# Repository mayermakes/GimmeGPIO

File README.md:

# GimmeGPIO
hardware to add GPIO to any PC running Linux

basic test, pins and pwm working
updated FW
python library working.
pushed changes.
case fits.

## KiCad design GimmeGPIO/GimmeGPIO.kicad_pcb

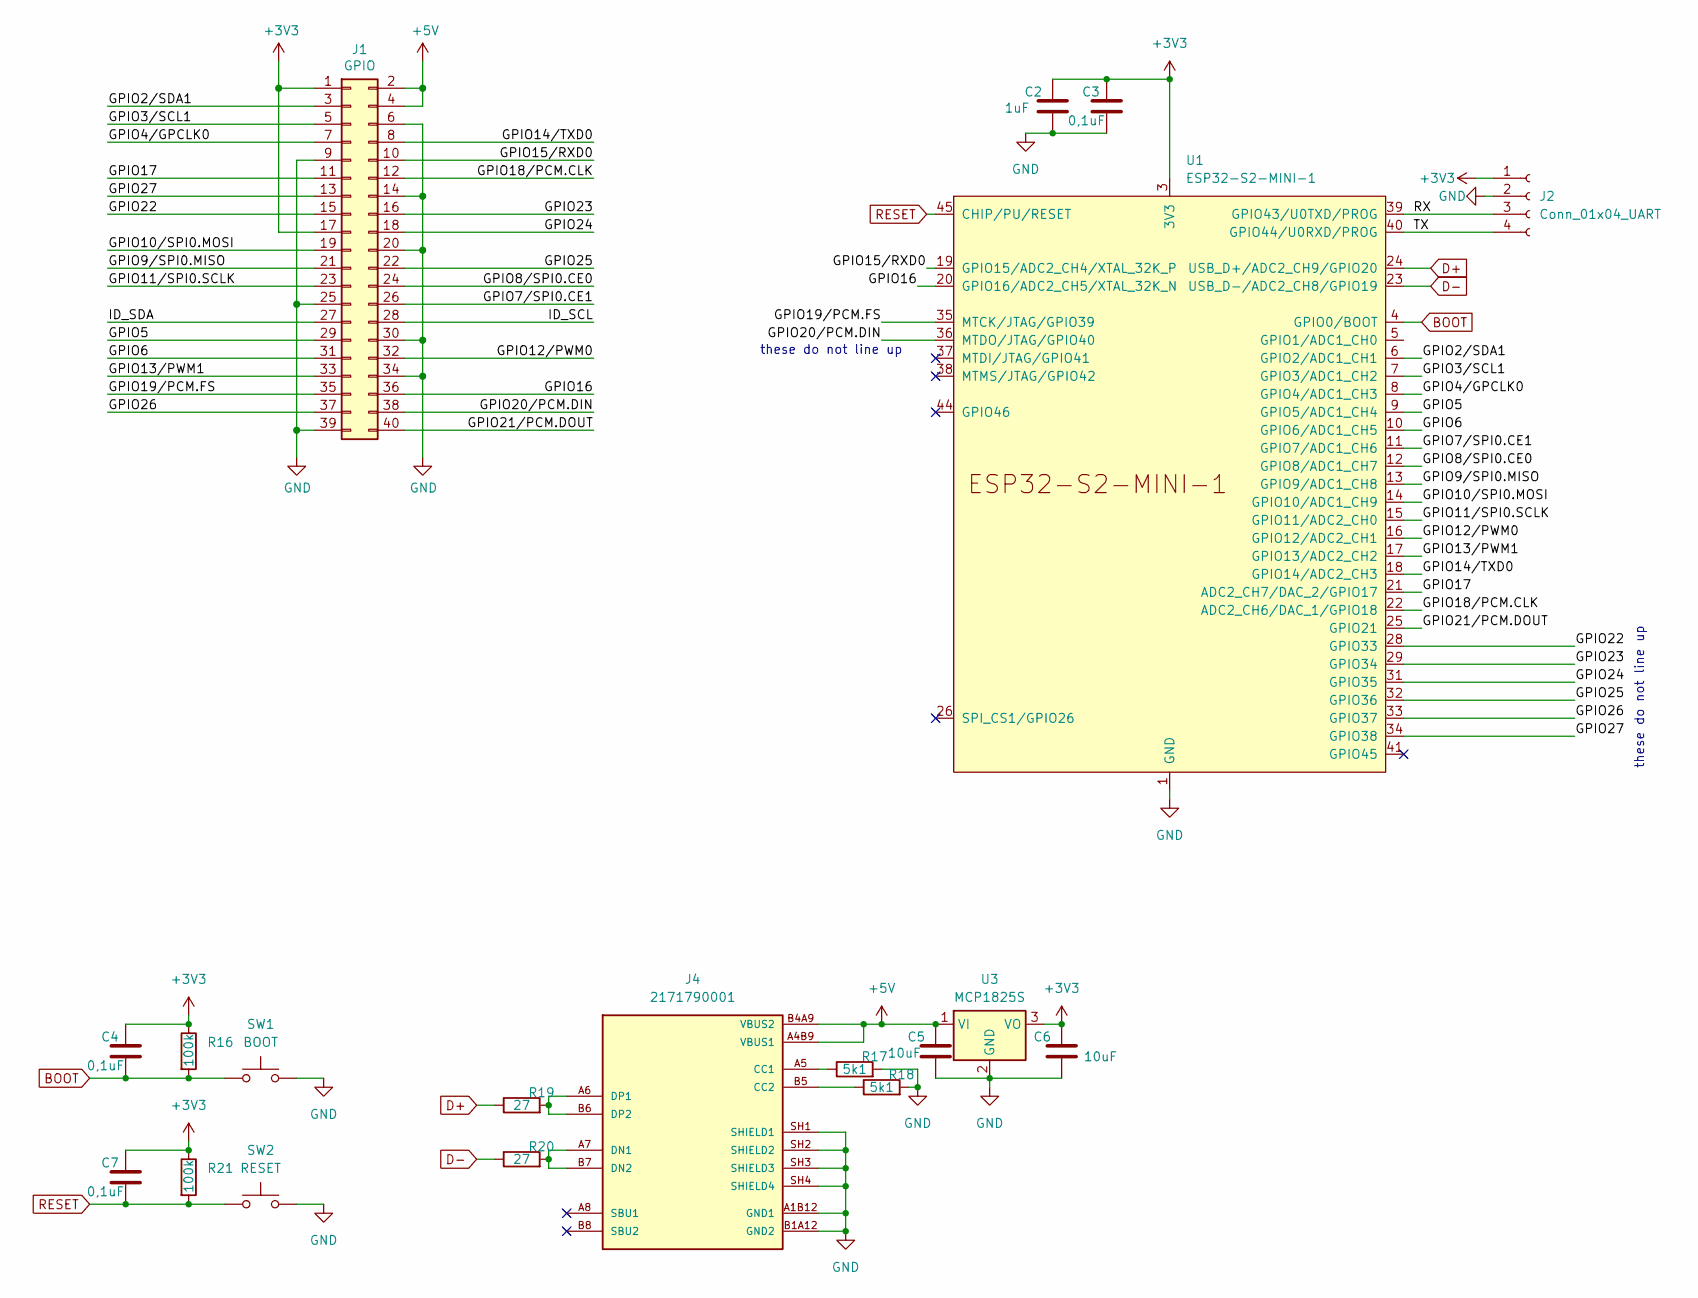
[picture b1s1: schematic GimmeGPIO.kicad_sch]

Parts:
C2: 1uF; C_0603_1608Metric
C3, C4, C7: 0,1uF; C_0603_1608Metric
C5, C6: 10uF; C_0603_1608Metric
J1: GPIO; PinSocket_2x20_P2.54mm_Vertical
J2: Conn_01x04_UART; PinHeader_1x04_P2.54mm_Vertical
J4: 2171790001; MOLEX_2171790001; PARTREV A1
R16, R21: 100k; R_0603_1608Metric
R17, R18: 5k1; R_0603_1608Metric
R19, R20: 27; R_0603_1608Metric
SW1: BOOT; SW_SPST_PTS810
SW2: RESET; SW_SPST_PTS810
U1: ESP32-S2-MINI-1; ESP32-S2-MINI-1U
U3: MCP1825S; SOT-223-3_TabPin2

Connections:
+3V3: C2.1, C3.1, C4.1, C6.1, C7.1, J1.1, J1.17, J2.1, R16.1, R21.1, U1.3 (3V3), U3.3 (VO)
+5V: C5.1, J1.2, J1.4, J4.A4B9 (VBUS1), J4.B4A9 (VBUS2), U3.1 (VI)
/GPIO2/SDA1: J1.3, U1.6 (GPIO2/ADC1_CH1)
/GPIO3/SCL1: J1.5, U1.7 (GPIO3/ADC1_CH2)
/GPIO4/GPCLK0: J1.7, U1.8 (GPIO4/ADC1_CH3)
/GPIO5: J1.29, U1.9 (GPIO5/ADC1_CH4)
/GPIO6: J1.31, U1.10 (GPIO6/ADC1_CH5)
/GPIO7/SPI0.CE1: J1.26, U1.11 (GPIO7/ADC1_CH6)
/GPIO8/SPI0.CE0: J1.24, U1.12 (GPIO8/ADC1_CH7)
/GPIO9/SPI0.MISO: J1.21, U1.13 (GPIO9/ADC1_CH8)
/GPIO10/SPI0.MOSI: J1.19, U1.14 (GPIO10/ADC1_CH9)
/GPIO11/SPI0.SCLK: J1.23, U1.15 (GPIO11/ADC2_CH0)
/GPIO12/PWM0: J1.32, U1.16 (GPIO12/ADC2_CH1)
/GPIO13/PWM1: J1.33, U1.17 (GPIO13/ADC2_CH2)
/GPIO14/TXD0: J1.8, U1.18 (GPIO14/ADC2_CH3)
/GPIO15/RXD0: J1.10, U1.19 (GPIO15/ADC2_CH4/XTAL_32K_P)
/GPIO16: J1.36, U1.20 (GPIO16/ADC2_CH5/XTAL_32K_N)
/GPIO17: J1.11, U1.21 (ADC2_CH7/DAC_2/GPIO17)
/GPIO18/PCM.CLK: J1.12, U1.22 (ADC2_CH6/DAC_1/GPIO18)
/GPIO19/PCM.FS: J1.35, U1.35 (MTCK/JTAG/GPIO39)
/GPIO20/PCM.DIN: J1.38, U1.36 (MTDO/JTAG/GPIO40)
/GPIO21/PCM.DOUT: J1.40, U1.25 (GPIO21)
/GPIO22: J1.15, U1.28 (GPIO33)
/GPIO23: J1.16, U1.29 (GPIO34)
/GPIO24: J1.18, U1.31 (GPIO35)
/GPIO25: J1.22, U1.32 (GPIO36)
/GPIO26: J1.37, U1.33 (GPIO37)
/GPIO27: J1.13, U1.34 (GPIO38)
/ID_SCL: J1.28
/ID_SDA: J1.27
/RX: J2.3, U1.39 (GPIO43/U0TXD/PROG)
/TX: J2.4, U1.40 (GPIO44/U0RXD/PROG)
BOOT: C4.2, R16.2, SW1.1, U1.4 (GPIO0/BOOT)
D+: R19.1, U1.24 (USB_D+/ADC2_CH9/GPIO20)
D-: R20.1, U1.23 (USB_D-/ADC2_CH8/GPIO19)
GND: C2.2, C3.2, C5.2, C6.2, J1.6, J1.9, J1.14, J1.20, J1.25, J1.30, J1.34, J1.39, J2.2, J4.A1B12 (GND1), J4.B1A12 (GND2), J4.SH1 (SHIELD1), J4.SH2 (SHIELD2), J4.SH3 (SHIELD3), J4.SH4 (SHIELD4), R17.2, R18.2, SW1.2, SW2.2, U1.1 (GND), U1.2 (GND), U1.30 (GND), U1.42 (GND), U1.43 (GND), U1.46 (GND), U1.47 (GND), U1.48 (GND), U1.49 (GND), U1.50 (GND), U1.51 (GND), U1.52 (GND), U1.53 (GND), U1.54 (GND), U1.55 (GND), U1.56 (GND), U1.57 (GND), U1.58 (GND), U1.59 (GND), U1.60 (GND), U1.61 (GND), U1.62 (GND), U1.63 (GND), U1.64 (GND), U1.65 (GND), U3.2 (GND)
unnamed: J4.A5 (CC1), R17.1
unnamed: J4.B5 (CC2), R18.1
unnamed: J4.A7 (DN1), J4.B7 (DN2), R20.2
unnamed: J4.A6 (DP1), J4.B6 (DP2), R19.2
RESET: C7.2, R21.2, SW2.1, U1.45 (CHIP/PU/RESET)

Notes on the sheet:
these do not line up

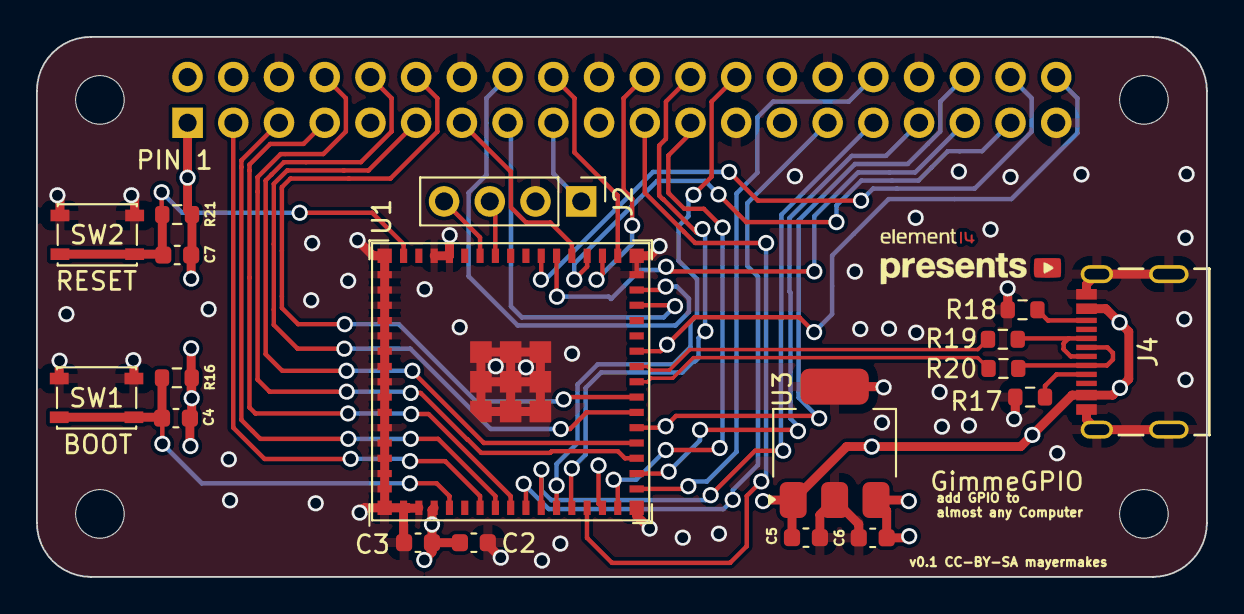
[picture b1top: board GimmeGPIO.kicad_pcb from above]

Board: 4 copper layers, 65.0 x 30.0 mm, 24 parts (1 on the bottom side), 39 nets.

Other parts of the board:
MH1, MH2, MH3, MH4: MountingHole_2.7mm_M2.5
Ref**: Val**; e14presents logo 10mm silk and copper v2

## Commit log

2025-09-14 as seen in video
2025-09-14 basic Plate case for 3dp/laser etc.
2025-09-14 initial untested stuff
2025-09-14 first sign of life
2025-09-16 update
    breaking changes
2025-09-16 partially tested FW
2025-09-16 new cad versions
    plate case confirmed fitting, standoffs unclear.

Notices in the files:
GimmeGPIO/GimmeGPIO.kicad_pcb:
v0.1 CC-BY-SA mayermakes
